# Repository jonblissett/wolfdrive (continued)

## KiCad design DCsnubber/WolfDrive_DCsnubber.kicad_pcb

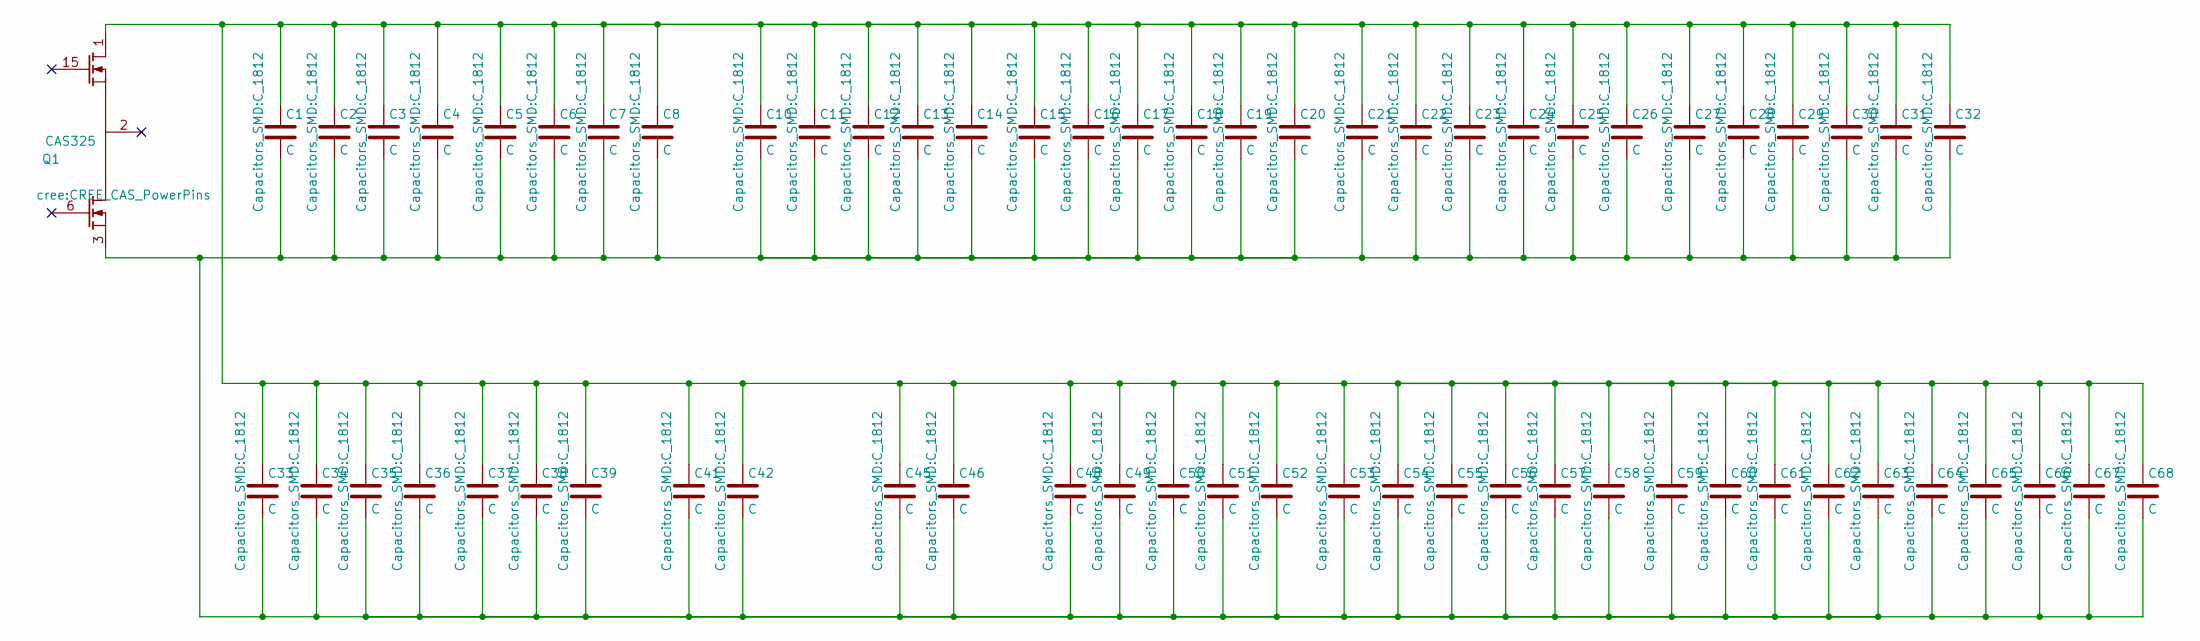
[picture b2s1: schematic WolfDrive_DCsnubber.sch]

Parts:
C1, C2, C3, C4, C5, C6, C7, C8, C10, C11, C12, C13, C14, C15, C16, C17, C18, C19, C20, C21, C22, C23, C24, C25, C26, C27, C28, C29, C30, C31, C32, C33, C34, C35, C36, C37, C38, C39, C41, C42, C45, C46, C48, C49, C50, C51, C52, C53, C54, C55, C56, C57, C58, C59, C60, C61, C62, C63, C64, C65, C66, C67, C68: C; C_1812
Q1: CAS325; CREE_CAS_PowerPins

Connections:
unnamed: C1.1, C2.1, C3.1, C4.1, C5.1, C6.1, C7.1, C8.1, C10.1, C11.1, C12.1, C13.1, C14.1, C15.1, C16.1, C17.1, C18.1, C19.1, C20.1, C21.1, C22.1, C23.1, C24.1, C25.1, C26.1, C27.1, C28.1, C29.1, C30.1, C31.1, C32.1, C33.1, C34.1, C35.1, C36.1, C37.1, C38.1, C39.1, C41.1, C42.1, C45.1, C46.1, C48.1, C49.1, C50.1, C51.1, C52.1, C53.1, C54.1, C55.1, C56.1, C57.1, C58.1, C59.1, C60.1, C61.1, C62.1, C63.1, C64.1, C65.1, C66.1, C67.1, C68.1, Q1.1 (D)
unnamed: C1.2, C2.2, C3.2, C4.2, C5.2, C6.2, C7.2, C8.2, C10.2, C11.2, C12.2, C13.2, C14.2, C15.2, C16.2, C17.2, C18.2, C19.2, C20.2, C21.2, C22.2, C23.2, C24.2, C25.2, C26.2, C27.2, C28.2, C29.2, C30.2, C31.2, C32.2, C33.2, C34.2, C35.2, C36.2, C37.2, C38.2, C39.2, C41.2, C42.2, C45.2, C46.2, C48.2, C49.2, C50.2, C51.2, C52.2, C53.2, C54.2, C55.2, C56.2, C57.2, C58.2, C59.2, C60.2, C61.2, C62.2, C63.2, C64.2, C65.2, C66.2, C67.2, C68.2, Q1.3 (S)

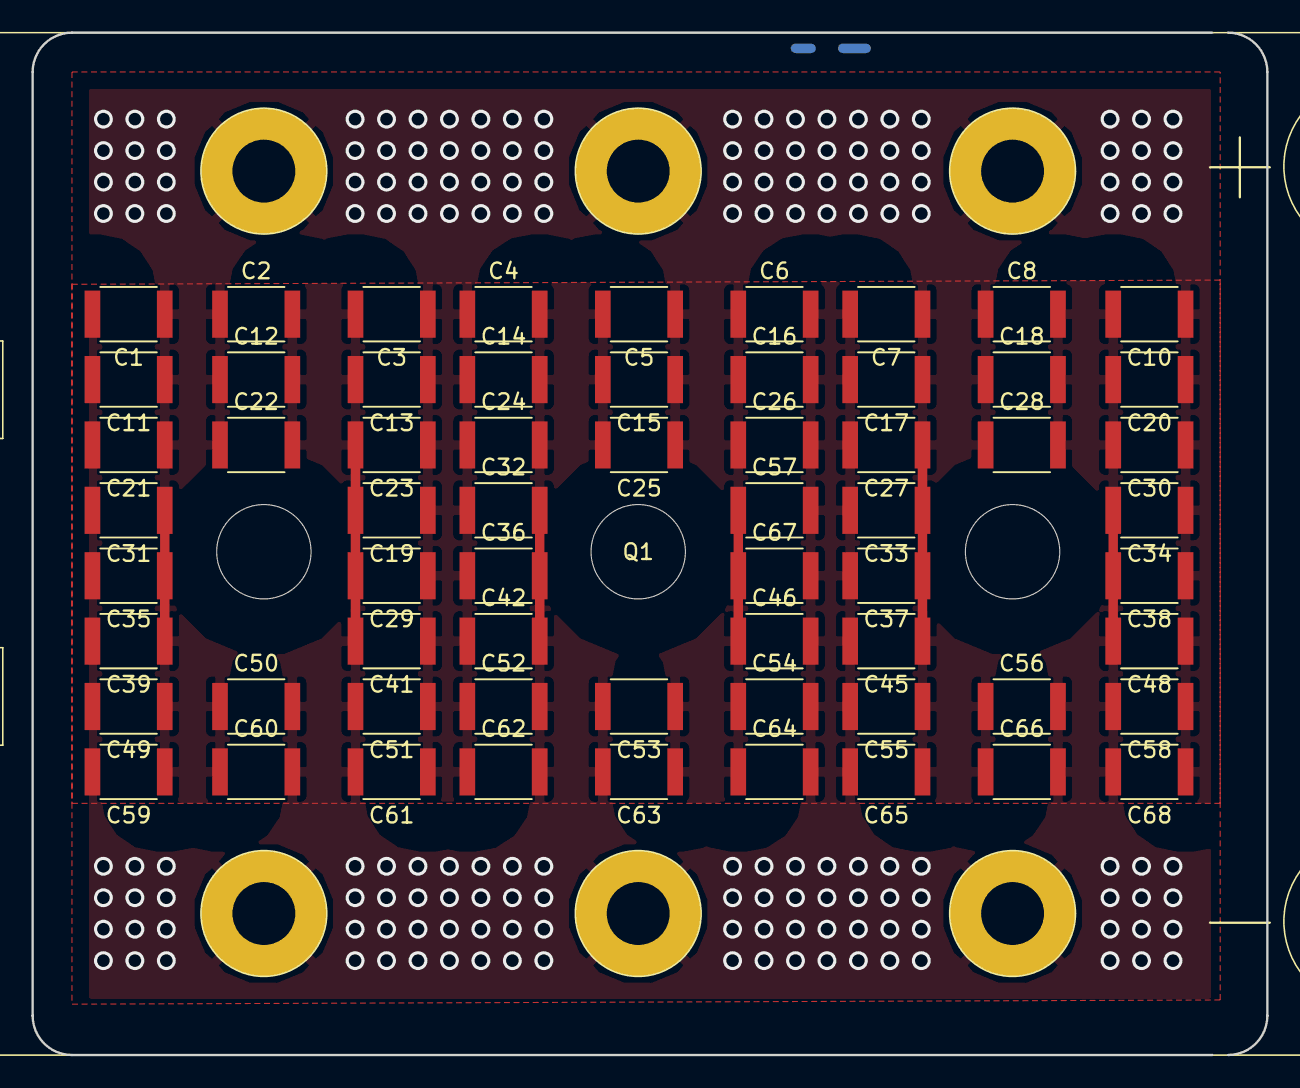
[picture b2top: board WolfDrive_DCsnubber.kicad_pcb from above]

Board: 2 copper layers, 78.5 x 65.0 mm, 64 parts (0 on the bottom side), 2 nets.

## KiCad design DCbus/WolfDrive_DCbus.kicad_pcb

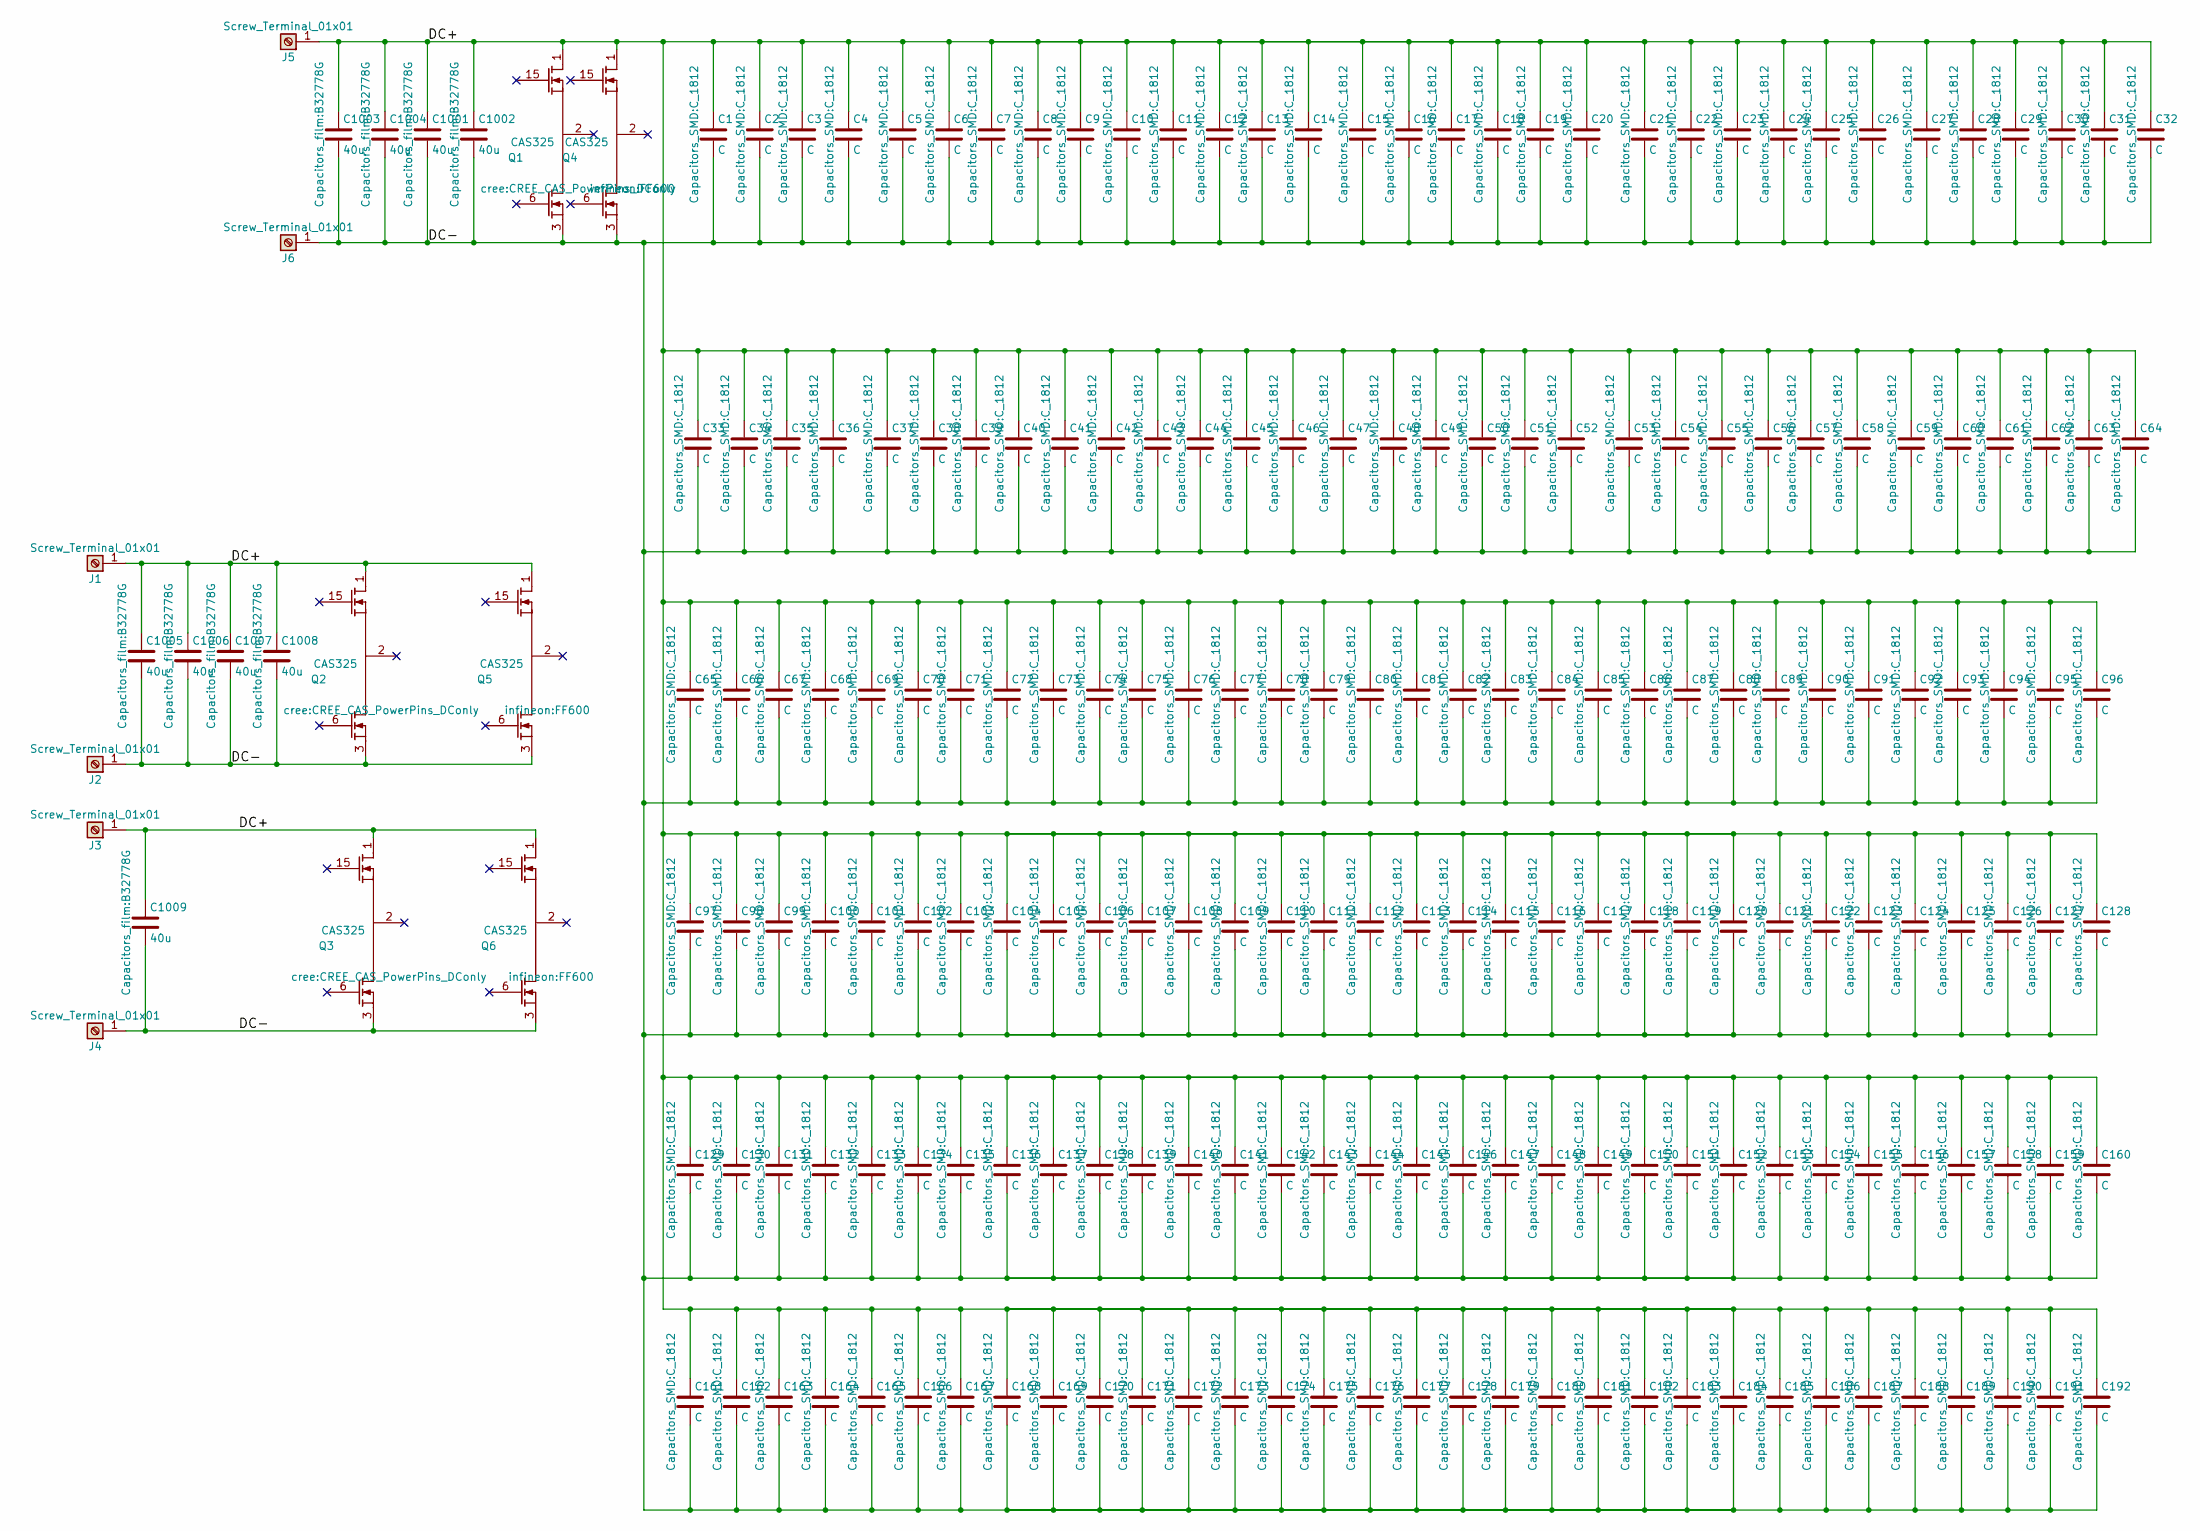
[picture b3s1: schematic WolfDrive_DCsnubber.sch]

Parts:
C1, C2, C3, C4, C5, C6, C7, C8, C9, C10, C11, C12, C13, C14, C15, C16, C17, C18, C19, C20, C21, C22, C23, C24, C25, C26, C27, C28, C29, C30, C31, C32, C33, C34, C35, C36, C37, C38, C39, C40, C41, C42, C43, C44, C45, C46, C47, C48, C49, C50, C51, C52, C53, C54, C55, C56, C57, C58, C59, C60, C61, C62, C63, C64, C65, C66, C67, C68, C69, C70, C71, C72, C73, C74, C75, C76, C77, C78, C79, C80, C81, C82, C83, C84, C85, C86, C87, C88, C89, C90, C91, C92, C93, C94, C95, C96, C97, C98, C99, C100, C101, C102, C103, C104, C105, C106, C107, C108, C109, C110, C111, C112, C113, C114, C115, C116, C117, C118, C119, C120, C121, C122, C123, C124, C125, C126, C127, C128, C129, C130, C131, C132, C133, C134, C135, C136, C137, C138, C139, C140, C141, C142, C143, C144, C145, C146, C147, C148, C149, C150, C151, C152, C153, C154, C155, C156, C157, C158, C159, C160, C161, C162, C163, C164, C165, C166, C167, C168, C169, C170, C171, C172, C173, C174, C175, C176, C177, C178, C179, C180, C181, C182, C183, C184, C185, C186, C187, C188, C189, C190, C191, C192: C; C_1812
C1001, C1002, C1003, C1004, C1005, C1006, C1007, C1008, C1009: 40u; B32778G
J1, J2, J3, J4, J5, J6: Screw_Terminal_01x01; PowerOne_16x16mm_24pin
Q1, Q2, Q3: CAS325; CREE_CAS_PowerPins_DConly
Q4, Q5, Q6: CAS325; FF600

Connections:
/DC+: C1.1, C2.1, C3.1, C4.1, C5.1, C6.1, C7.1, C8.1, C9.1, C10.1, C11.1, C12.1, C13.1, C14.1, C15.1, C16.1, C17.1, C18.1, C19.1, C20.1, C21.1, C22.1, C23.1, C24.1, C25.1, C26.1, C27.1, C28.1, C29.1, C30.1, C31.1, C32.1, C33.1, C34.1, C35.1, C36.1, C37.1, C38.1, C39.1, C40.1, C41.1, C42.1, C43.1, C44.1, C45.1, C46.1, C47.1, C48.1, C49.1, C50.1, C51.1, C52.1, C53.1, C54.1, C55.1, C56.1, C57.1, C58.1, C59.1, C60.1, C61.1, C62.1, C63.1, C64.1, C65.1, C66.1, C67.1, C68.1, C69.1, C70.1, C71.1, C72.1, C73.1, C74.1, C75.1, C76.1, C77.1, C78.1, C79.1, C80.1, C81.1, C82.1, C83.1, C84.1, C85.1, C86.1, C87.1, C88.1, C89.1, C90.1, C91.1, C92.1, C93.1, C94.1, C95.1, C96.1, C97.1, C98.1, C99.1, C100.1, C101.1, C102.1, C103.1, C104.1, C105.1, C106.1, C107.1, C108.1, C109.1, C110.1, C111.1, C112.1, C113.1, C114.1, C115.1, C116.1, C117.1, C118.1, C119.1, C120.1, C121.1, C122.1, C123.1, C124.1, C125.1, C126.1, C127.1, C128.1, C129.1, C130.1, C131.1, C132.1, C133.1, C134.1, C135.1, C136.1, C137.1, C138.1, C139.1, C140.1, C141.1, C142.1, C143.1, C144.1, C145.1, C146.1, C147.1, C148.1, C149.1, C150.1, C151.1, C152.1, C153.1, C154.1, C155.1, C156.1, C157.1, C158.1, C159.1, C160.1, C161.1, C162.1, C163.1, C164.1, C165.1, C166.1, C167.1, C168.1, C169.1, C170.1, C171.1, C172.1, C173.1, C174.1, C175.1, C176.1, C177.1, C178.1, C179.1, C180.1, C181.1, C182.1, C183.1, C184.1, C185.1, C186.1, C187.1, C188.1, C189.1, C190.1, C191.1, C192.1, C1001.1, C1002.1, C1003.1, C1004.1, C1005.1, C1006.1, C1007.1, C1008.1, C1009.1, J1.1, J3.1, J5.1, Q1.1 (D), Q2.1 (D), Q3.1 (D), Q4.1 (D), Q5.1 (D), Q6.1 (D); also elsewhere on the board
/DC-: C1.2, C2.2, C3.2, C4.2, C5.2, C6.2, C7.2, C8.2, C9.2, C10.2, C11.2, C12.2, C13.2, C14.2, C15.2, C16.2, C17.2, C18.2, C19.2, C20.2, C21.2, C22.2, C23.2, C24.2, C25.2, C26.2, C27.2, C28.2, C29.2, C30.2, C31.2, C32.2, C33.2, C34.2, C35.2, C36.2, C37.2, C38.2, C39.2, C40.2, C41.2, C42.2, C43.2, C44.2, C45.2, C46.2, C47.2, C48.2, C49.2, C50.2, C51.2, C52.2, C53.2, C54.2, C55.2, C56.2, C57.2, C58.2, C59.2, C60.2, C61.2, C62.2, C63.2, C64.2, C65.2, C66.2, C67.2, C68.2, C69.2, C70.2, C71.2, C72.2, C73.2, C74.2, C75.2, C76.2, C77.2, C78.2, C79.2, C80.2, C81.2, C82.2, C83.2, C84.2, C85.2, C86.2, C87.2, C88.2, C89.2, C90.2, C91.2, C92.2, C93.2, C94.2, C95.2, C96.2, C97.2, C98.2, C99.2, C100.2, C101.2, C102.2, C103.2, C104.2, C105.2, C106.2, C107.2, C108.2, C109.2, C110.2, C111.2, C112.2, C113.2, C114.2, C115.2, C116.2, C117.2, C118.2, C119.2, C120.2, C121.2, C122.2, C123.2, C124.2, C125.2, C126.2, C127.2, C128.2, C129.2, C130.2, C131.2, C132.2, C133.2, C134.2, C135.2, C136.2, C137.2, C138.2, C139.2, C140.2, C141.2, C142.2, C143.2, C144.2, C145.2, C146.2, C147.2, C148.2, C149.2, C150.2, C151.2, C152.2, C153.2, C154.2, C155.2, C156.2, C157.2, C158.2, C159.2, C160.2, C161.2, C162.2, C163.2, C164.2, C165.2, C166.2, C167.2, C168.2, C169.2, C170.2, C171.2, C172.2, C173.2, C174.2, C175.2, C176.2, C177.2, C178.2, C179.2, C180.2, C181.2, C182.2, C183.2, C184.2, C185.2, C186.2, C187.2, C188.2, C189.2, C190.2, C191.2, C192.2, C1001.2, C1002.2, C1003.2, C1004.2, C1005.2, C1006.2, C1007.2, C1008.2, C1009.2, J2.1, J4.1, J6.1, Q1.3 (S), Q2.3 (S), Q3.3 (S), Q4.3 (S), Q5.3 (S), Q6.3 (S); also elsewhere on the board

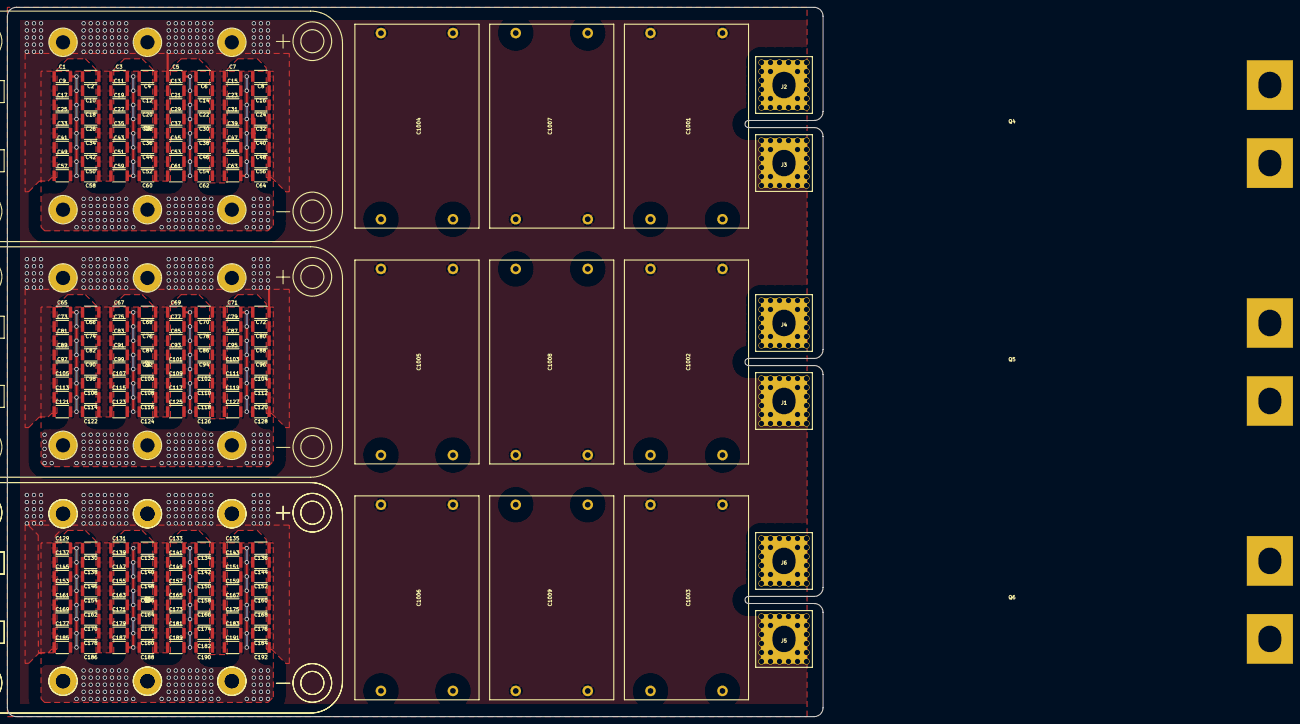
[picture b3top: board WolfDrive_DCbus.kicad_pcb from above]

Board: 2 copper layers, 230.0 x 200.0 mm, 214 parts (0 on the bottom side), 2 nets.

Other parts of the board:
Q2#2: CAS325; CREE_CAS_PowerPins_DConly

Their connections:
/DC+: Q2#2.1; also elsewhere on the board
/DC-: Q2#2.3; also elsewhere on the board

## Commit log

2018-03-06 Create LICENSE
2018-03-06 Initial commit - untested
2018-03-08 Housekeeping, missed label dxf added
2018-03-08 edited gitignore
2018-03-08 .gitignore is now working
2018-03-12 Added extra SPI to pin assignment, combine with QSPI
2018-03-13 added missing testpoint labels to silk
2018-03-13 grounded test on FT232RL, issue #2
2018-03-14 work towards fixing v0.1 issues, 1-5
2018-03-14 Added input voltage protection
2018-03-14 Amended input protection
2018-03-14 updated footprints
2018-03-14 fixed duplicate gates in U10
2018-03-14 PCB layout progress for issues <5
2018-03-15 Major PCB layout revision for v0.2
2018-03-15 Finished layout, silk sceen amended
2018-03-15 Updated fabrication files for v0.2
2018-03-15 Minor edits before fabricating v0.2
2018-03-15 Updated schematic for v0.2
2018-04-26 first steps, PWM test
2018-04-26 first steps, adding periphials
2018-06-24 Firmware framework, work in progress
2018-06-24 Added misc drawings
2018-06-24 Removed schematic copied from current sensor repo
2018-06-24 organised drawings
2018-06-24 removed superflous CAD/CAM files
2018-06-26 Encoder to analogue adapter code
2018-06-26 Pins amended for using DAC with SPI1
2018-06-26 Library fix for KiCAD v5
2018-06-26 Compatibility for AkSim2 encoder, 13b ACK length
2018-06-28 Pay attention to angle error correction with switching frequency
